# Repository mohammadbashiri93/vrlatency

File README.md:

# VRLatency: Virtual Reality Latency Measurement 
Tests go here

## What is it
VRLatency is a python package that provides an easy way, both in terms of hardware design and software usability, to measure and analyze the latency of any projector-based virtual reality system. In fact, with this package, along the device, one can measure the latency of any display.

## TODO
- Test tracking and total experiment with the new changes

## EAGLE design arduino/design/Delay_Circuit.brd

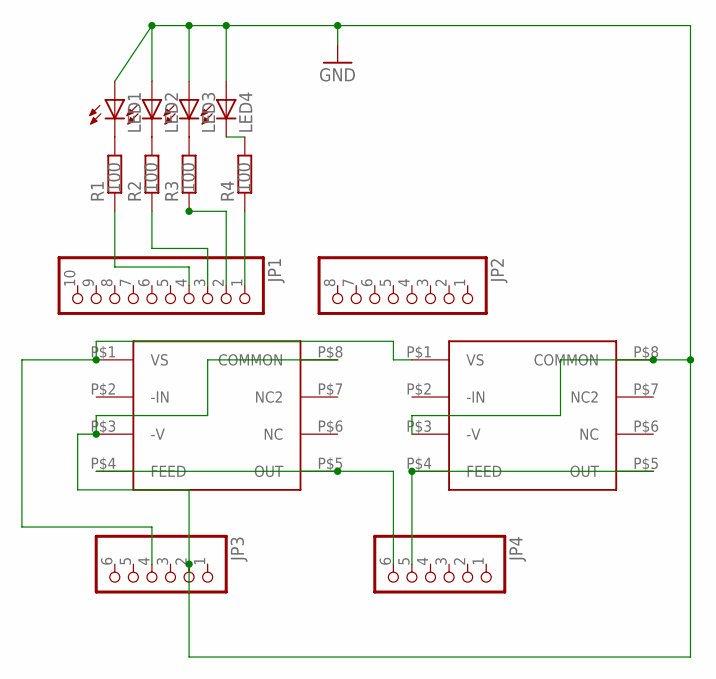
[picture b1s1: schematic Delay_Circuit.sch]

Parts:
JP1: PINHD-1X10; 1X10
JP2: PINHD-1X8; 1X08
JP3, JP4: PINHD-1X6; 1X06
LED1, LED2, LED3, LED4: LED5MM
OPT101_1, OPT101_2: OPT101P
R1, R2, R3, R4: 100; 0204/7

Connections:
GND: JP3.2, LED1.A, LED2.A, LED3.A, LED4.A, OPT101_1.P$3 (-V), OPT101_1.P$8 (COMMON), OPT101_2.P$3 (-V), OPT101_2.P$8 (COMMON)
unnamed: LED2.K (C), R2.2
unnamed: LED1.K (C), R1.2
unnamed: LED3.K (C), R3.2
unnamed: LED4.K (C), R4.2
unnamed: JP1.1, R4.1
unnamed: JP1.2, R3.1
unnamed: JP1.3, R2.1
unnamed: JP1.4, R1.1
unnamed: JP3.4, OPT101_1.P$1 (VS), OPT101_2.P$1 (VS)
unnamed: JP4.6, OPT101_1.P$4 (FEED), OPT101_1.P$5 (OUT)
unnamed: JP4.5, OPT101_2.P$4 (FEED), OPT101_2.P$5 (OUT)

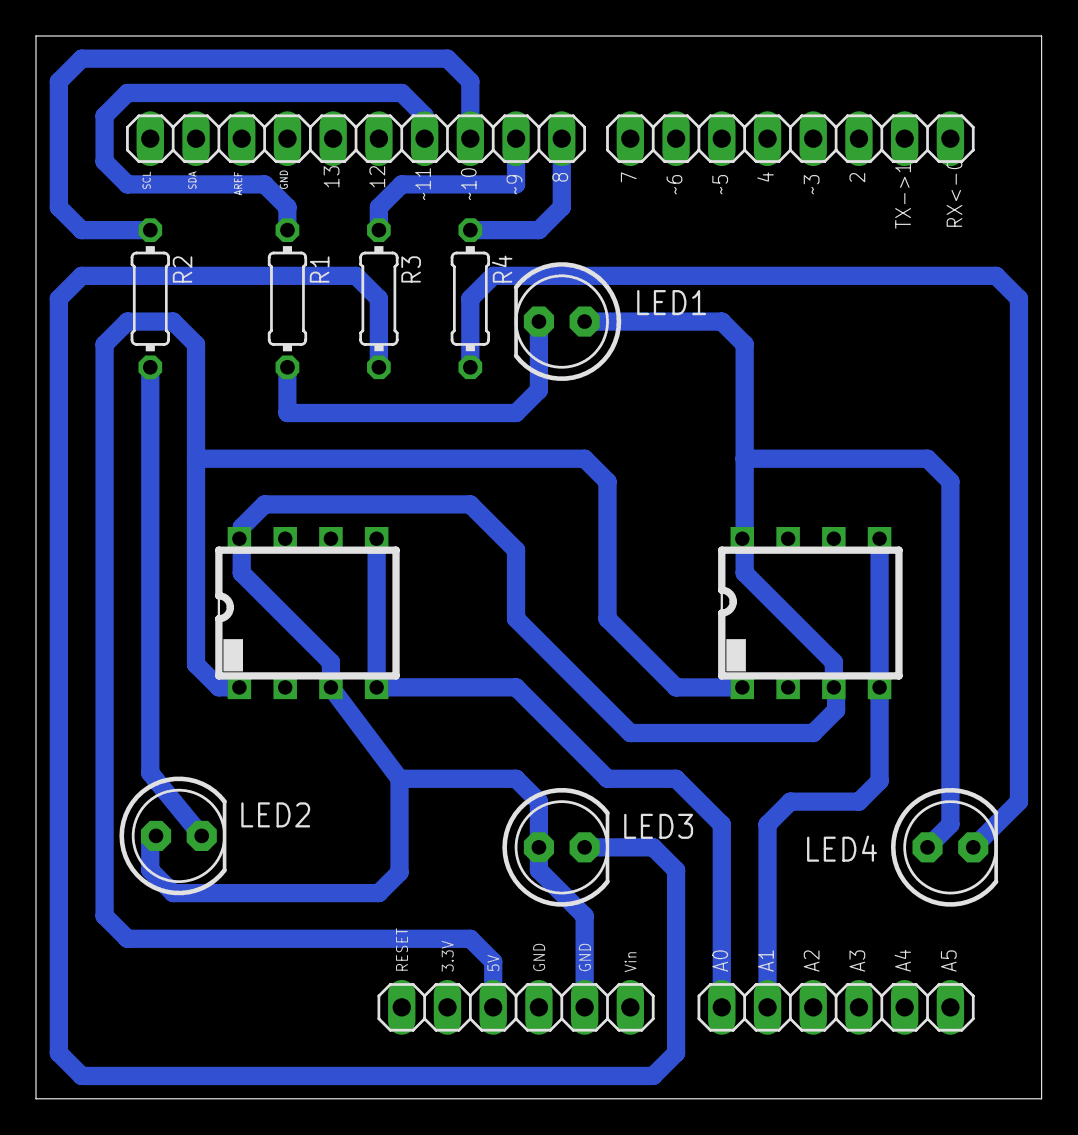
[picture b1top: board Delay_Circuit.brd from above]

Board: 2 copper layers, 55.9 x 59.0 mm, 14 parts (0 on the bottom side), 12 nets.

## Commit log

2018-09-08 Added circuit details for arduino shield
2018-09-11 updating the notebook
2018-09-11 working on the notebook and integrating the methods into analysis script
2018-09-12 using the display method in the cmd_api
2018-09-12 refactoring the analysis script
2018-09-17 no o of the plotting functions take Pandas DataFrame as an input now
2018-09-17 working on the report notebook
2018-09-17 changes to notebook, as well as changing samplesize for arduino mega
2018-09-17 resolved merge conflict
2018-09-17 updated the display experiment
2018-09-17 recording display experiment
2018-09-17 Arduino is crazy fast now!
2018-09-18 trials now get clustered based on the SSE
2018-09-19 testing different display signal acquisition with the faster arduino
2018-09-19 analysis pipeline runs now without error. on finding the index of the trough of residuals, sometimes we are faced with a situation we the slope of the brightness transtion is different. and if the te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
    With regards to the length of the signals for computing the residuals, the length of the reference signal is now forced to be equal to the test signal
2018-09-19 Tracking experiment running
2018-09-20 Total experiment running
